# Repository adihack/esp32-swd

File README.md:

# esp-swd

**esp-swd** is an ESP32-S3 based dual-target SWD flasher and UART bridge with DUT isolation: open hardware, firmware,
a portable C library and a Python host library. It is built for CI and production benches, where a probe stays
plugged in for weeks and flashes the same known 3.3 V targets over and over.

The r5 board sits between a host PC (USB-C) and a device under test (DUT) that carries two MCUs, one per channel.
It does three things:
- programs each MCU over its own SWD port;
- bridges each DUT UART to the host;
- on command, opens analog switches on every DUT line, so the DUT's sleep current can be measured without leakage
  through the tool.

## Status (2026-11-11): MVP
Firmware 0.5.0 (protocol 5) with the `esw` host tools covers the first usable scope:
- **Two SWD channels**, two DUTs flashed at once: `esw flash A=app.hex B=fw.hex`.
- **Two DUT UARTs as terminal devices**, up to 1 Mbaud each, full duplex: the daemon `esw serve` serves them as
  `ttyA`/`ttyB` for picocom, minicom, screen, pyserial and the like.
- **Isolation control:**
  - semi-automatic: the switches close only while used and only with the DUT powered;
  - direct: switch modes `auto`/`on`/`off` per group, from the CLI or Python.
- **Firmware update over USB:** `esw update`, esptool through the chip's USB-Serial-JTAG. No buttons, and it
  recovers even a hung firmware.

Usage: **`host/python/README.md`**. State, open items and next steps: **`docs/status.md`**. Hardware tests:
**`docs/testing.md`**. Everything below is tested on hardware.

Earlier results (board r5, channel A, nRF52840 DK):
- **Isolation interlock:** VTref is checked before any signal switch closes. The switches reopen on VTref loss, host
  loss, reboot and firmware panic.
- **SWD engines:** an ESP32-S3 dedicated-GPIO engine up to 8 MHz (10 MHz cap), and a portable bit-bang fallback.
  Soak: about 3 M packets each at 8 MHz and 10 MHz, 0 errors.
- **Flashing:** 1 MB of random data on an nRF52840 takes **3.42 s** in total: mass erase 0.17 s, program 3.08 s,
  on-target CRC-32 verify 0.17 s. The data path is PC → USB → ESP32-S3 → SWD → NVMC.
- **UART bridge (channel A):** byte-exact at 115200, 460800 and 1 Mbaud, full duplex.
  - A 1 MB stream arrived intact while SWD reads ran in parallel and the host stopped reading for 250 ms.
  - With the switches open nothing gets through, and writes are refused.
- **Firmware update:** `idf.py flash` over USB while the firmware runs; two OTA slots with rollback.
- **Target modules (2026-11-10):** nRF52, **nRF5340** (application and network core) and **STM32U575/585**, plus a
  generic Cortex-M fallback. Measured, erase + program + on-target CRC verify: nRF5340 1 MB app image 3.2 s, network
  core 256 KB 0.71 s; STM32U585 2 MB 7.0 s through a streaming RAM loader (322 KB/s), a real 1.2 MB image 4.2 s;
  RDP level 1 → 0 unlock tested.
- **Parallel channels:** one SWD worker per channel on its own CPU core. nRF5340 + STM32U585 flashed at once:
  5.5 s against 7.5 s one after the other (now limited by the USB-Serial-JTAG link, about 485 KB/s).

- **Host daemon and TTYs (2026-11-11):** ttyA ↔ ttyB cabled across the two UART headers, both directions at once,
  byte-exact at up to 2 Mbaud; at 1 Mbaud (97 KB/s each way) also while both DUTs flash. Both DUTs at once with
  `esw flash`: 5.6 s against 8.6 s one after the other.
  Programs share the board through the daemon (per-channel ownership, cleanup after a crash), and it survives board
  reboots and firmware updates.

| Not done yet |
|---|
| SWO |
| USB-OTG (TinyUSB): native CDC TTYs, vendor bulk interface, optional CMSIS-DAP v2; OTA over the protocol |
| STM32U5 with TrustZone on, external-flash loaders on the streaming ABI, nRF5340 network-core fast path test |
| multi-day soak |

Hardware is frozen at r5 (design revision d, JLCPCB, 2026-10-23). The two assembled boards carry
ESP32-S3-WROOM-1-**N4** modules (4 MB flash, no PSRAM), not the N16 in the BOM.

## Repository layout
| Path | Content |
|---|---|
| `lib/` | **Portable C11 library**: SWD/ADIv5, Cortex-M control, generic RAM-loader runtime (call and streaming ABIs), on-target CRC verify, target-module interface and the nRF52 module, isolation interlock, framed host protocol. No RTOS, no malloc. See `lib/README.md` |
| `ports/esp32s3/` | ESP32-S3 port: dedicated-GPIO SWD engine, pins, ADC, clock |
| `boards/r5/` | r5 board layer: pin map, switch groups, VTref divider, safe defaults |
| `app/` | ESP-IDF v6 firmware for r5 (USB-Serial-JTAG transport). See `app/README.md` |
| `host/python/` | Python host library and CLI (`esw`), daemon with the TTY bridge (`esw serve`), examples: flashing, speed test, PHY benchmark, UART and TTY self-tests, robustness checks. See `host/python/README.md` |
| `host/udev/`, `host/systemd/` | udev rule for the board; systemd user unit for the daemon |
| `loaders/` | Target-side loader sources; `crc32/build.py` (built-in CRC loader) and `stm32u5/build.py` (STM32U5 streaming flash loader) rebuild and verify them in an emulator |
| `testfw/` | Bare-metal test firmware for DUTs, e.g. `nrf52840_uart/` for the UART hardware test |
| `tests/` | Host unit tests against a bit-level SWD target simulator (`tests/sim/`); CI in `.github/workflows/ci.yml` |
| `docs/status.md`, `docs/testing.md` | **Start here for a new session:** status, decisions, next steps; every test with wiring and last results |
| `docs/hardware-reference.md` | **Start here for hardware.** Pin map, signal chains, polarities, connectors, test pads, interlock rules, boot notes, bring-up results |
| `docs/firmware-architecture.md` | Firmware architecture, reliability plan, milestones, decisions |
| `docs/hardware/` | Design brief, hardware architecture history, PCB layout notes |
| `docs/datasheets/` | Links to the vendor datasheets (not redistributed) |
| `hardware/rev5/` | r5 schematic PDF, KiCad 10 project as built, the exact JLCPCB production package |
| `firmware/bringup/`, `firmware/poc_swd/` | MicroPython bring-up blink and the first SWD board test (kept for reference) |

## New machine
Linux (Ubuntu or similar), Python ≥ 3.9. From a fresh clone:
```
git clone https://github.com/adihack/esp32-swd.git && cd esp32-swd

# 1. Python venv: build tools, host tools (`esw`), esptool; unicorn/capstone only for rebuilding loaders
python3 -m venv .venv
.venv/bin/pip install cmake ninja pyserial esptool unicorn capstone
.venv/bin/pip install -e host/python

# 2. USB access without sudo, no ModemManager probing (then re-plug the board)
sudo cp host/udev/60-esp-swd.rules /etc/udev/rules.d/ && sudo udevadm control --reload && sudo udevadm trigger

# 3. Library tests (no hardware)
PATH=$PWD/.venv/bin:$PATH cmake -S . -B build -G Ninja && cmake --build build && ctest --test-dir build
.venv/bin/python -m unittest discover -s host/python/tests

# 4. Firmware: ESP-IDF v6.0.3 (about 5 GB with tools)
git clone -b v6.0.3 --recursive https://github.com/espressif/esp-idf.git ~/esp/esp-idf-v6.0.3
~/esp/esp-idf-v6.0.3/install.sh esp32s3
. ~/esp/esp-idf-v6.0.3/export.sh && export PATH="$PATH:$PWD/.venv/bin"   # append the venv, never prepend
(cd app && idf.py build)
.venv/bin/esw update app/build          # or: cd app && idf.py -p /dev/ttyACM0 flash
.venv/bin/esw info
```
- No buttons are needed: USB-Serial-JTAG resets the chip into the ROM downloader in hardware. The board
  enumerates as `303a:1001`.
- Optional: the Arm GNU toolchain (15.3.rel2, from developer.arm.com, unpacked to
  `~/arm/arm-gnu-toolchain-15.3.rel2-x86_64-arm-none-eabi`, or set `ARM_GCC_BIN`). Needed only to rebuild the
  target-side loaders (`loaders/*/build.py`) and the DUT test firmware (`testfw/`, used by `uart_test.py`).

**Where to go next:** `docs/status.md` (where the project stands, what is next), `docs/testing.md` (every hardware
test with wiring and expected results), `host/python/README.md` (using `esw`).

## Quick start
```
esw serve &                                         # TTYs: $XDG_RUNTIME_DIR/esp-swd/<board>/ttyA, ttyB
esw info                                            # channels, switches, modes, TTYs
esw flash A=app.hex B=stm32.hex                     # both channels at once, CRC-verified
esw flash A1=net.hex                                # nRF5340 network core
esw mode B uart off                                 # isolation switch modes: auto | on | off
esw update app/build                                # board firmware over USB
esw stop                                            # stop the daemon
```
Examples (they also run through the daemon; wiring and expected results in `docs/testing.md`):
```
.venv/bin/python host/python/examples/flash_image.py --info --channel B      # identify a target, print its memory map
.venv/bin/python host/python/examples/parallel_flash.py --a app_a.hex --b app_b.hex   # benchmark, both channels
.venv/bin/python host/python/examples/tty_loopback.py --cross               # UART A <-> B through the TTYs
.venv/bin/python host/python/examples/nrf52_blinky.py --channel A          # nRF52840 DK: flash and watch it run
```
nRF5340: flash only images with Nordic's startup code (see `app/README.md`, "nRF5340 APPROTECT trap").
`--allow-erase` mass-erases a locked chip; without it, a locked chip is left alone.

## Hardware in one screen
| Function | Channel A | Channel B |
|---|---|---|
| SWDIO / SWCLK | GPIO4 / GPIO5 | GPIO11 / GPIO12 |
| SWO (in) | GPIO6 | GPIO14 |
| nRESET drive (high = assert) / sense | GPIO7 / GPIO15 | GPIO21 / GPIO47 |
| UART TX / RX | GPIO16 / GPIO17 | GPIO48 / GPIO35 |
| VTref ADC (reads VTref/2) | GPIO8 (ADC1_CH7) | GPIO1 (ADC1_CH0) |
| EN_SWD / EN_UART / EN_VTREF (active high) | GPIO9 / GPIO46 / GPIO10 | GPIO40 / GPIO41 / GPIO42 |

- Status LED: GPIO2, active high.
- USB: native, on GPIO19/20.
- No buttons.
- DUT I/O is 3.3 V only; there are no level translators.
- Every switch is **open by default** (100 kΩ pull-downs on the enables).
- Firmware must close EN_VTREF and see the DUT powered **before** closing the SWD or UART groups. Otherwise the tool
  back-powers an unpowered DUT.

All details, with the reasons, are in `docs/hardware-reference.md`.

## License
MIT, see `LICENSE`. This covers the firmware, library, host tools, documentation and the r5 hardware design files.
Vendor datasheets and the USB-C connector's 3D model are not part of the repository; see `docs/datasheets/README.md`.

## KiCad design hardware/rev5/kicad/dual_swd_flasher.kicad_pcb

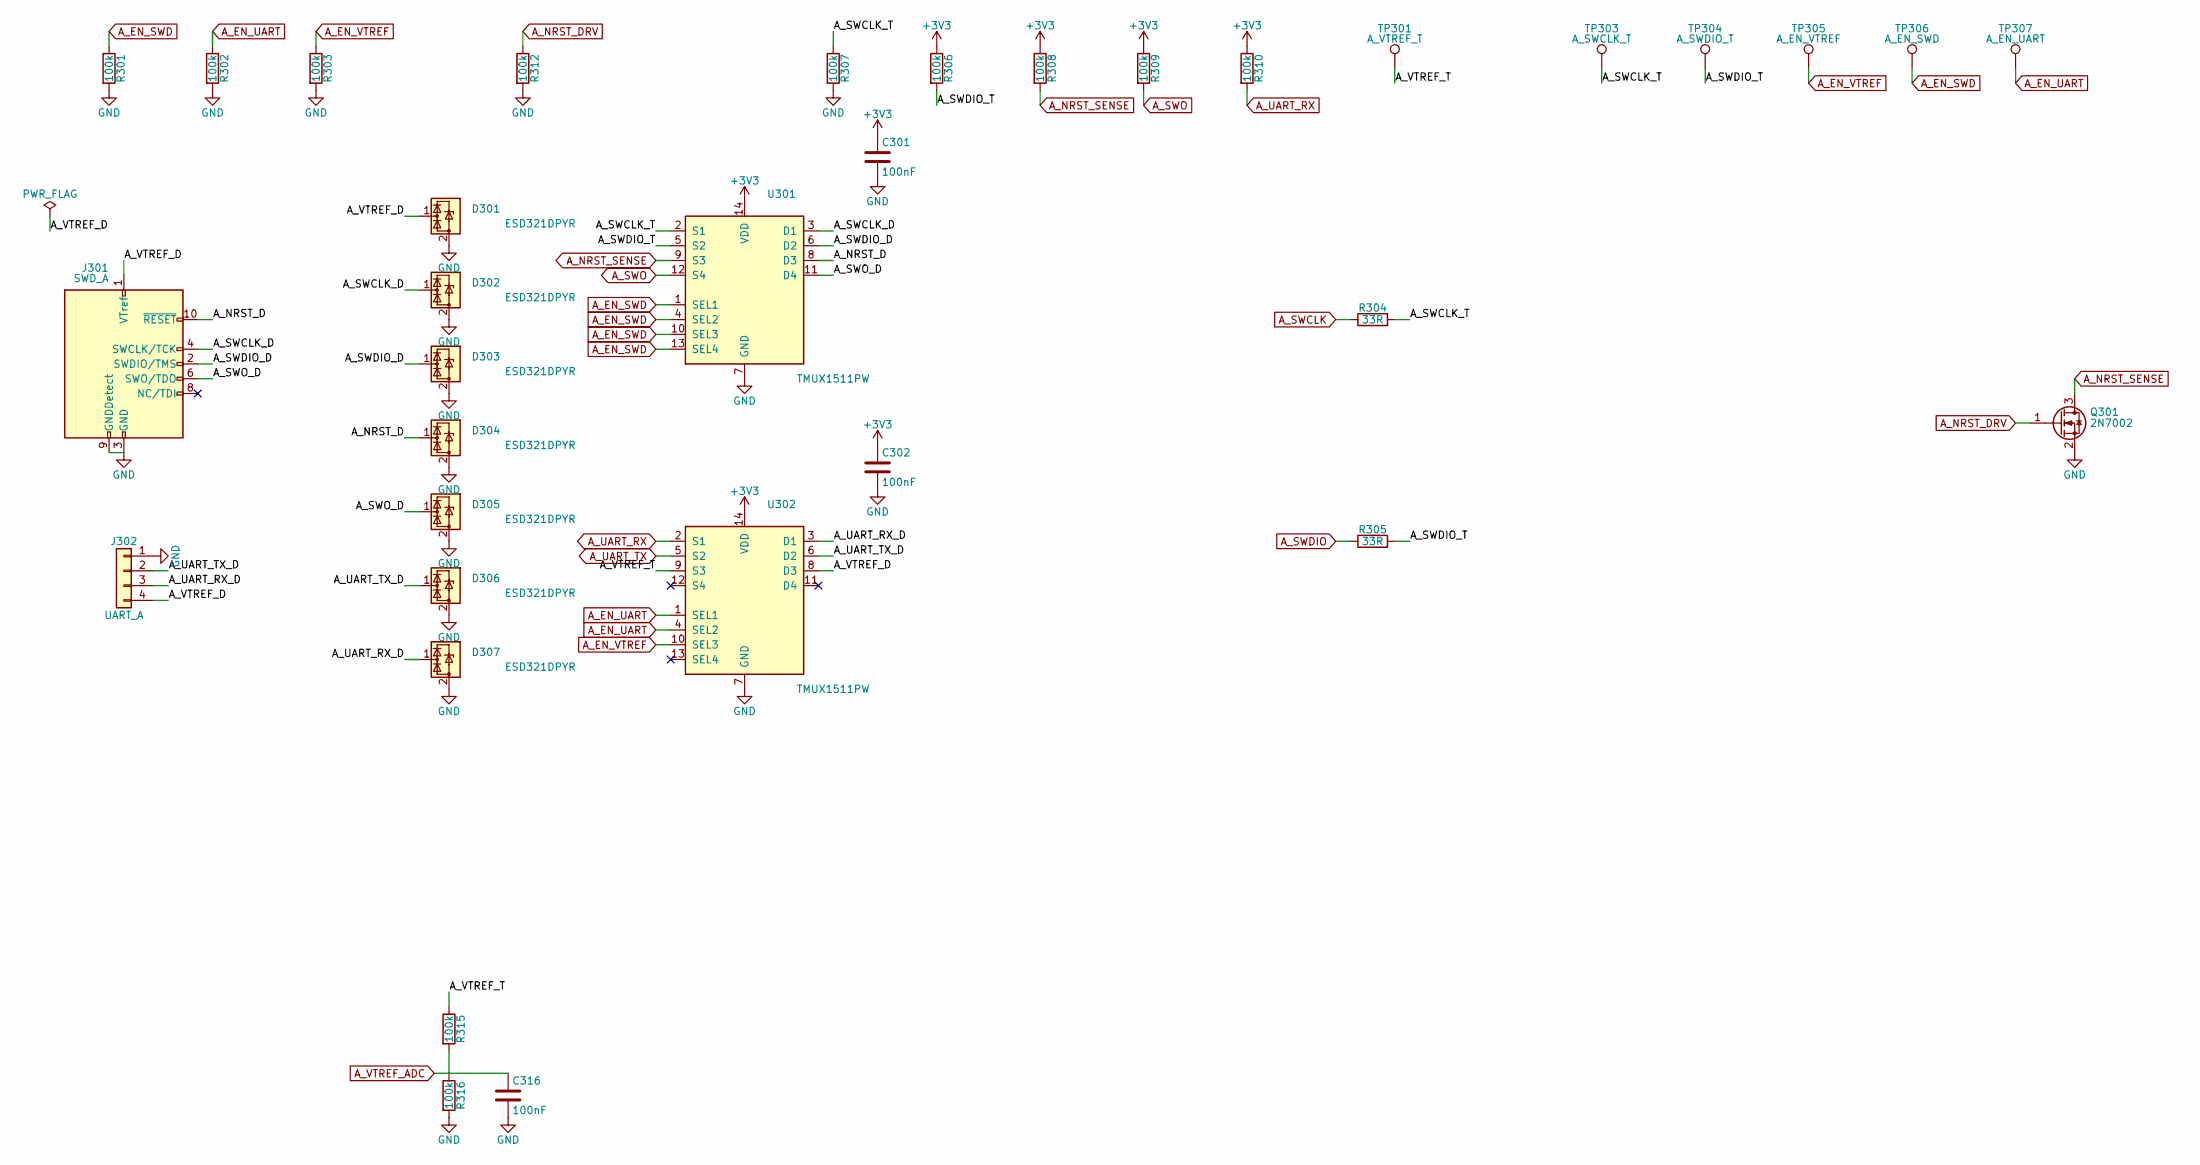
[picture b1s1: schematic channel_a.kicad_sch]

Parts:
C301, C302, C316: 100nF; C_0402_1005Metric; LCSC C1525
D301, D302, D303, D304, D305, D306, D307: ESD321DPYR; Texas_DPY0002A_0.6x1mm_P0.65mm; LCSC C2868952
J301: SWD_A; PinHeader_2x05_P1.27mm_Vertical_SMD; LCSC C3975188
J302: UART_A; PinHeader_1x04_P2.54mm_Vertical; LCSC C2691448
Q301: 2N7002; SOT-23; LCSC C8545
R301, R302, R303, R306, R307, R308, R309, R310, R312, R315, R316: 100k; R_0402_1005Metric; LCSC C25741
R304, R305: 33R; R_0402_1005Metric; LCSC C25105
TP301: A_VTREF_T; TestPoint_Pad_D1.0mm
TP303: A_SWCLK_T; TestPoint_Pad_D1.0mm
TP304: A_SWDIO_T; TestPoint_Pad_D1.0mm
TP305: A_EN_VTREF; TestPoint_Pad_D1.0mm
TP306: A_EN_SWD; TestPoint_Pad_D1.0mm
TP307: A_EN_UART; TestPoint_Pad_D1.0mm
U301, U302: TMUX1511PW; TSSOP-14_4.4x5mm_P0.65mm; LCSC C2866750

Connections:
+3V3: C301.1, C302.1, R306.1, R308.1, R309.1, R310.1, U301.14 (VDD), U302.14 (VDD); also elsewhere on the board
/Channel A/A_NRST_D: D304.1 (I/O), J301.10 (~RESET), U301.8 (D3)
/Channel A/A_SWCLK_D: D302.1 (I/O), J301.4 (SWCLK/TCK), U301.3 (D1)
/Channel A/A_SWCLK_T: R304.2, R307.1, TP303.1 (1_1), U301.2 (S1)
/Channel A/A_SWDIO_D: D303.1 (I/O), J301.2 (SWDIO/TMS), U301.6 (D2)
/Channel A/A_SWDIO_T: R305.2, R306.2, TP304.1 (1_1), U301.5 (S2)
/Channel A/A_SWO_D: D305.1 (I/O), J301.6 (SWO/TDO), U301.11 (D4)
/Channel A/A_UART_RX_D: D307.1 (I/O), J302.3, U302.3 (D1)
/Channel A/A_UART_TX_D: D306.1 (I/O), J302.2, U302.6 (D2)
/Channel A/A_VTREF_D: D301.1 (I/O), J301.1 (VTref), J302.4, U302.8 (D3)
/Channel A/A_VTREF_T: R315.1, TP301.1 (1_1), U302.9 (S3)
A_EN_SWD: R301.1, TP306.1 (1_1), U301.1 (SEL1), U301.4 (SEL2), U301.10 (SEL3), U301.13 (SEL4); also elsewhere on the board
A_EN_UART: R302.1, TP307.1 (1_1), U302.1 (SEL1), U302.4 (SEL2); also elsewhere on the board
A_EN_VTREF: R303.1, TP305.1 (1_1), U302.10 (SEL3); also elsewhere on the board
A_NRST_DRV: Q301.1 (G), R312.1; also elsewhere on the board
A_NRST_SENSE: Q301.3 (D), R308.2, U301.9 (S3); also elsewhere on the board
A_SWCLK: R304.1; also elsewhere on the board
A_SWDIO: R305.1; also elsewhere on the board
A_SWO: R309.2, U301.12 (S4); also elsewhere on the board
A_UART_RX: R310.2, U302.2 (S1); also elsewhere on the board
A_UART_TX: U302.5 (S2); also elsewhere on the board
A_VTREF_ADC: C316.1, R315.2, R316.1; also elsewhere on the board
GND: C301.2, C302.2, C316.2, D301.2 (GND), D302.2 (GND), D303.2 (GND), D304.2 (GND), D305.2 (GND), D306.2 (GND), D307.2 (GND), J301.3 (GND), J301.5 (GND), J301.9 (GNDDetect), J302.1, Q301.2 (S), R301.2, R302.2, R303.2, R307.2, R312.2, R316.2, U301.7 (GND), U302.7 (GND); also elsewhere on the board

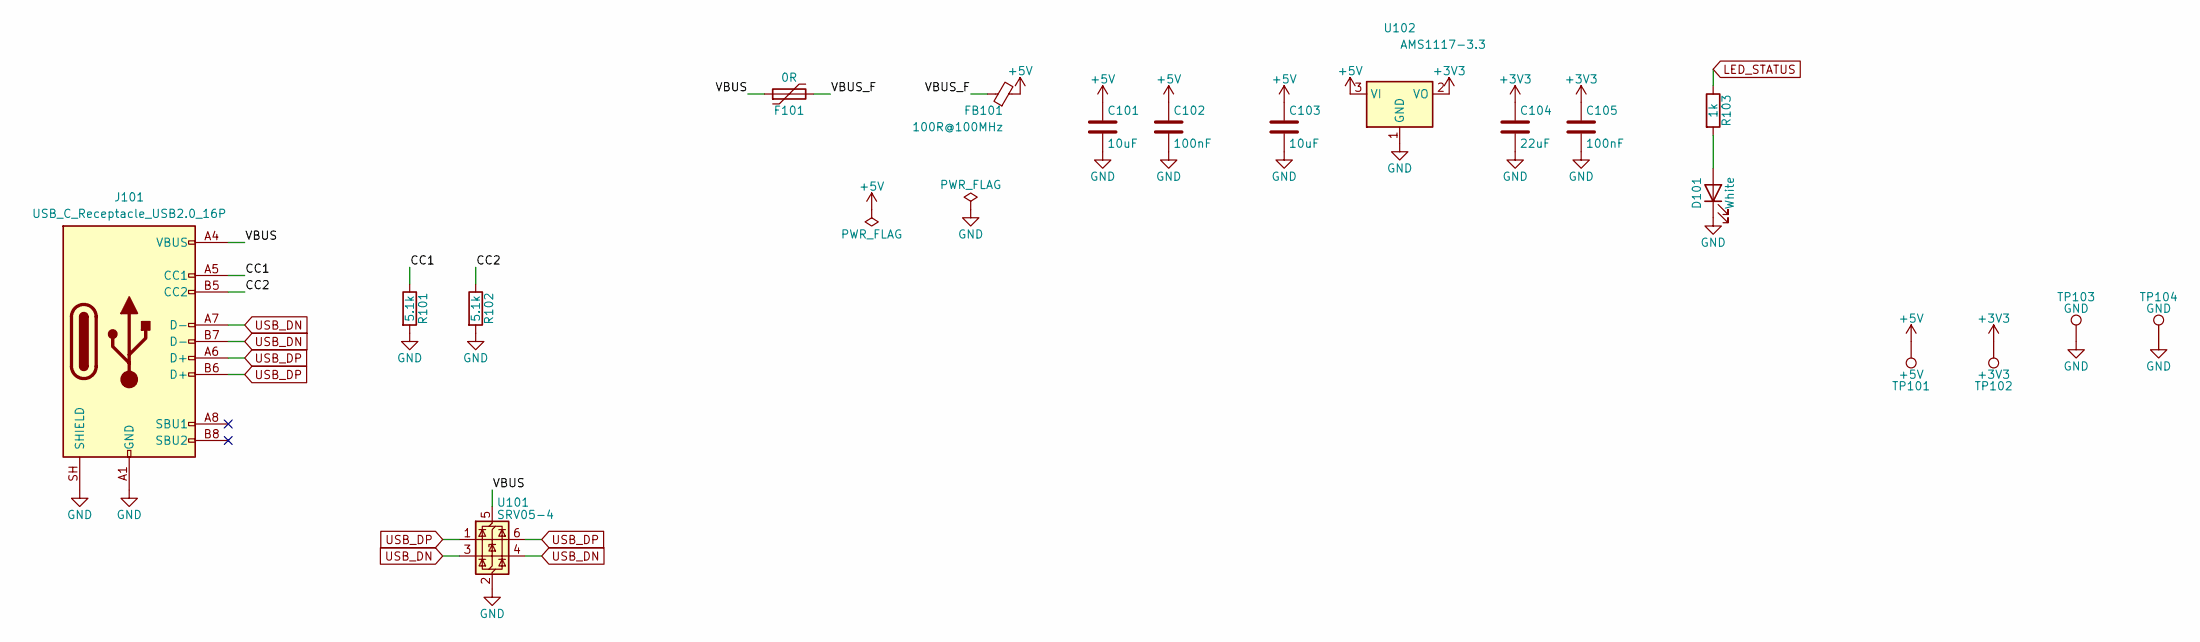
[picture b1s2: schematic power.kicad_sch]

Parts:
C101, C103: 10uF; C_0805_2012Metric; LCSC C15850
C102, C105: 100nF; C_0402_1005Metric; LCSC C1525
C104: 22uF; C_0805_2012Metric; LCSC C45783
D101: White; LED_0603_1608Metric; LCSC C2290
F101: 0R; Fuse_1206_3216Metric; LCSC C17888
FB101: 100R@100MHz; L_0805_2012Metric; LCSC C1015
J101: USB_C_Receptacle_USB2.0_16P; USB_C_Receptacle_HRO_TYPE-C-31-M-12; LCSC C165948
R101, R102: 5.1k; R_0402_1005Metric; LCSC C25905
R103: 1k; R_0402_1005Metric; LCSC C11702
TP101: +5V; TestPoint_Pad_D1.0mm
TP102: +3V3; TestPoint_Pad_D1.0mm
TP103, TP104: GND; TestPoint_Pad_D1.0mm
U101: SRV05-4; SOT-23-6; LCSC C7420376
U102: AMS1117-3.3; SOT-223-3_TabPin2; LCSC C6186

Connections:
+3V3: C104.1, C105.1, TP102.1 (1_1), U102.2 (VO); also elsewhere on the board
+5V: C101.1, C102.1, C103.1, FB101.2, TP101.1 (1_1), U102.3 (VI); also elsewhere on the board
/Power/CC1: J101.A5 (CC1), R101.1
/Power/CC2: J101.B5 (CC2), R102.1
/Power/VBUS: F101.1, J101.A4 (VBUS), J101.A9 (VBUS), J101.B4 (VBUS), J101.B9 (VBUS), U101.5 (VBUS)
/Power/VBUS_F: F101.2, FB101.1
GND: C101.2, C102.2, C103.2, C104.2, C105.2, D101.1 (K), J101.A1 (GND), J101.A12 (GND), J101.B1 (GND), J101.B12 (GND), J101.SH (SHIELD), R101.2, R102.2, TP103.1 (1_1), TP104.1 (1_1), U101.2 (GND), U102.1 (GND); also elsewhere on the board
LED_STATUS: R103.1; also elsewhere on the board
unnamed: D101.2 (A), R103.2
USB_DN: J101.A7 (D-), J101.B7 (D-), U101.3 (I/O2), U101.4 (I/O2); also elsewhere on the board
USB_DP: J101.A6 (D+), J101.B6 (D+), U101.1 (I/O1), U101.6 (I/O1); also elsewhere on the board

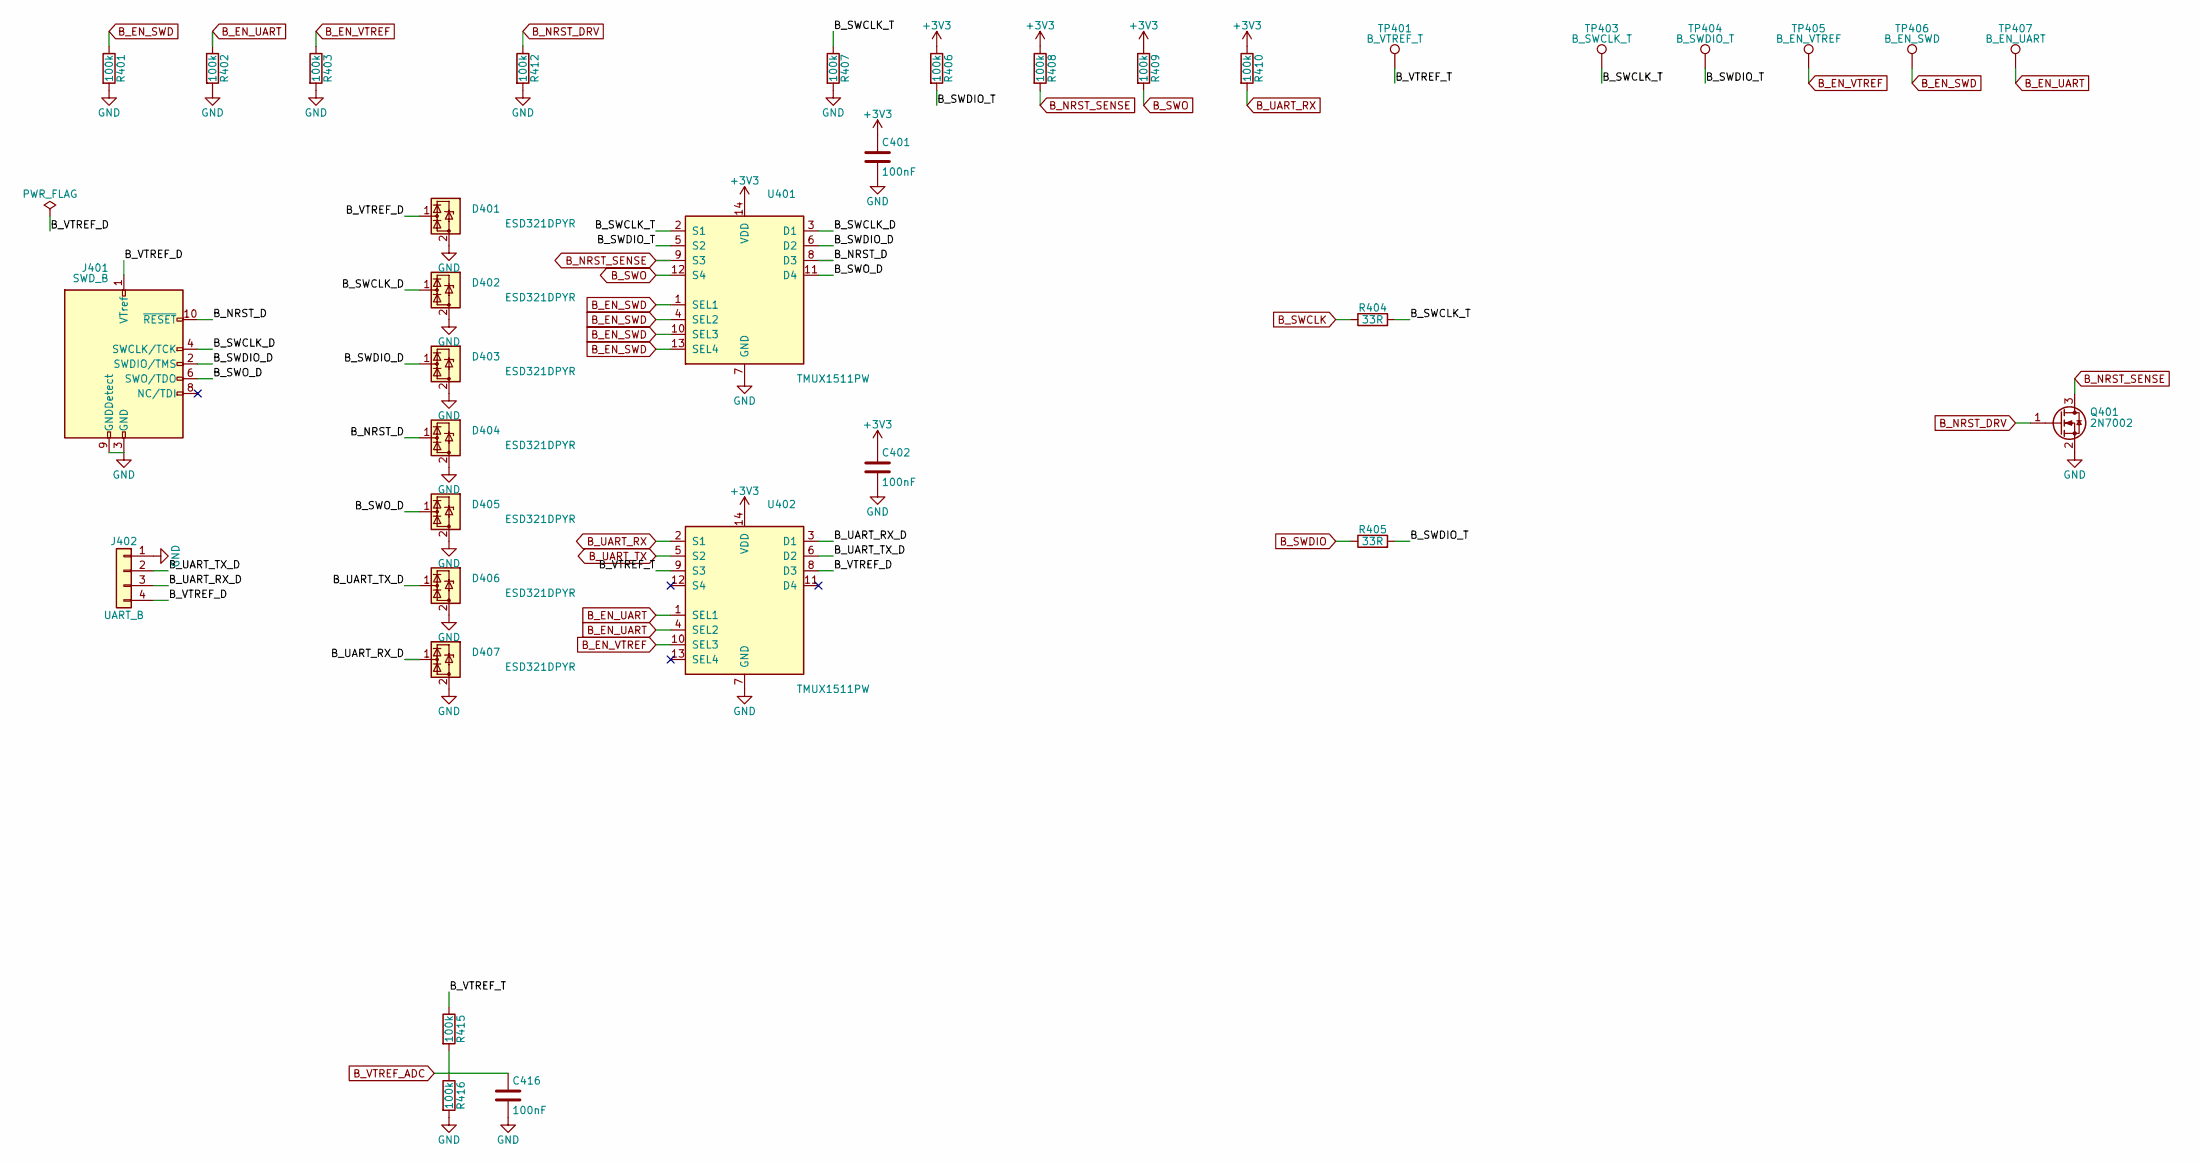
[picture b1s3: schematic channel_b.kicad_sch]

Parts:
C401, C402, C416: 100nF; C_0402_1005Metric; LCSC C1525
D401, D402, D403, D404, D405, D406, D407: ESD321DPYR; Texas_DPY0002A_0.6x1mm_P0.65mm; LCSC C2868952
J401: SWD_B; PinHeader_2x05_P1.27mm_Vertical_SMD; LCSC C3975188
J402: UART_B; PinHeader_1x04_P2.54mm_Vertical; LCSC C2691448
Q401: 2N7002; SOT-23; LCSC C8545
R401, R402, R403, R406, R407, R408, R409, R410, R412, R415, R416: 100k; R_0402_1005Metric; LCSC C25741
R404, R405: 33R; R_0402_1005Metric; LCSC C25105
TP401: B_VTREF_T; TestPoint_Pad_D1.0mm
TP403: B_SWCLK_T; TestPoint_Pad_D1.0mm
TP404: B_SWDIO_T; TestPoint_Pad_D1.0mm
TP405: B_EN_VTREF; TestPoint_Pad_D1.0mm
TP406: B_EN_SWD; TestPoint_Pad_D1.0mm
TP407: B_EN_UART; TestPoint_Pad_D1.0mm
U401, U402: TMUX1511PW; TSSOP-14_4.4x5mm_P0.65mm; LCSC C2866750

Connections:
+3V3: C401.1, C402.1, R406.1, R408.1, R409.1, R410.1, U401.14 (VDD), U402.14 (VDD); also elsewhere on the board
/Channel B/B_NRST_D: D404.1 (I/O), J401.10 (~RESET), U401.8 (D3)
/Channel B/B_SWCLK_D: D402.1 (I/O), J401.4 (SWCLK/TCK), U401.3 (D1)
/Channel B/B_SWCLK_T: R404.2, R407.1, TP403.1 (1_1), U401.2 (S1)
/Channel B/B_SWDIO_D: D403.1 (I/O), J401.2 (SWDIO/TMS), U401.6 (D2)
/Channel B/B_SWDIO_T: R405.2, R406.2, TP404.1 (1_1), U401.5 (S2)
/Channel B/B_SWO_D: D405.1 (I/O), J401.6 (SWO/TDO), U401.11 (D4)
/Channel B/B_UART_RX_D: D407.1 (I/O), J402.3, U402.3 (D1)
/Channel B/B_UART_TX_D: D406.1 (I/O), J402.2, U402.6 (D2)
/Channel B/B_VTREF_D: D401.1 (I/O), J401.1 (VTref), J402.4, U402.8 (D3)
/Channel B/B_VTREF_T: R415.1, TP401.1 (1_1), U402.9 (S3)
B_EN_SWD: R401.1, TP406.1 (1_1), U401.1 (SEL1), U401.4 (SEL2), U401.10 (SEL3), U401.13 (SEL4); also elsewhere on the board
B_EN_UART: R402.1, TP407.1 (1_1), U402.1 (SEL1), U402.4 (SEL2); also elsewhere on the board
B_EN_VTREF: R403.1, TP405.1 (1_1), U402.10 (SEL3); also elsewhere on the board
B_NRST_DRV: Q401.1 (G), R412.1; also elsewhere on the board
B_NRST_SENSE: Q401.3 (D), R408.2, U401.9 (S3); also elsewhere on the board
B_SWCLK: R404.1; also elsewhere on the board
B_SWDIO: R405.1; also elsewhere on the board
B_SWO: R409.2, U401.12 (S4); also elsewhere on the board
B_UART_RX: R410.2, U402.2 (S1); also elsewhere on the board
B_UART_TX: U402.5 (S2); also elsewhere on the board
B_VTREF_ADC: C416.1, R415.2, R416.1; also elsewhere on the board
GND: C401.2, C402.2, C416.2, D401.2 (GND), D402.2 (GND), D403.2 (GND), D404.2 (GND), D405.2 (GND), D406.2 (GND), D407.2 (GND), J401.3 (GND), J401.5 (GND), J401.9 (GNDDetect), J402.1, Q401.2 (S), R401.2, R402.2, R403.2, R407.2, R412.2, R416.2, U401.7 (GND), U402.7 (GND); also elsewhere on the board

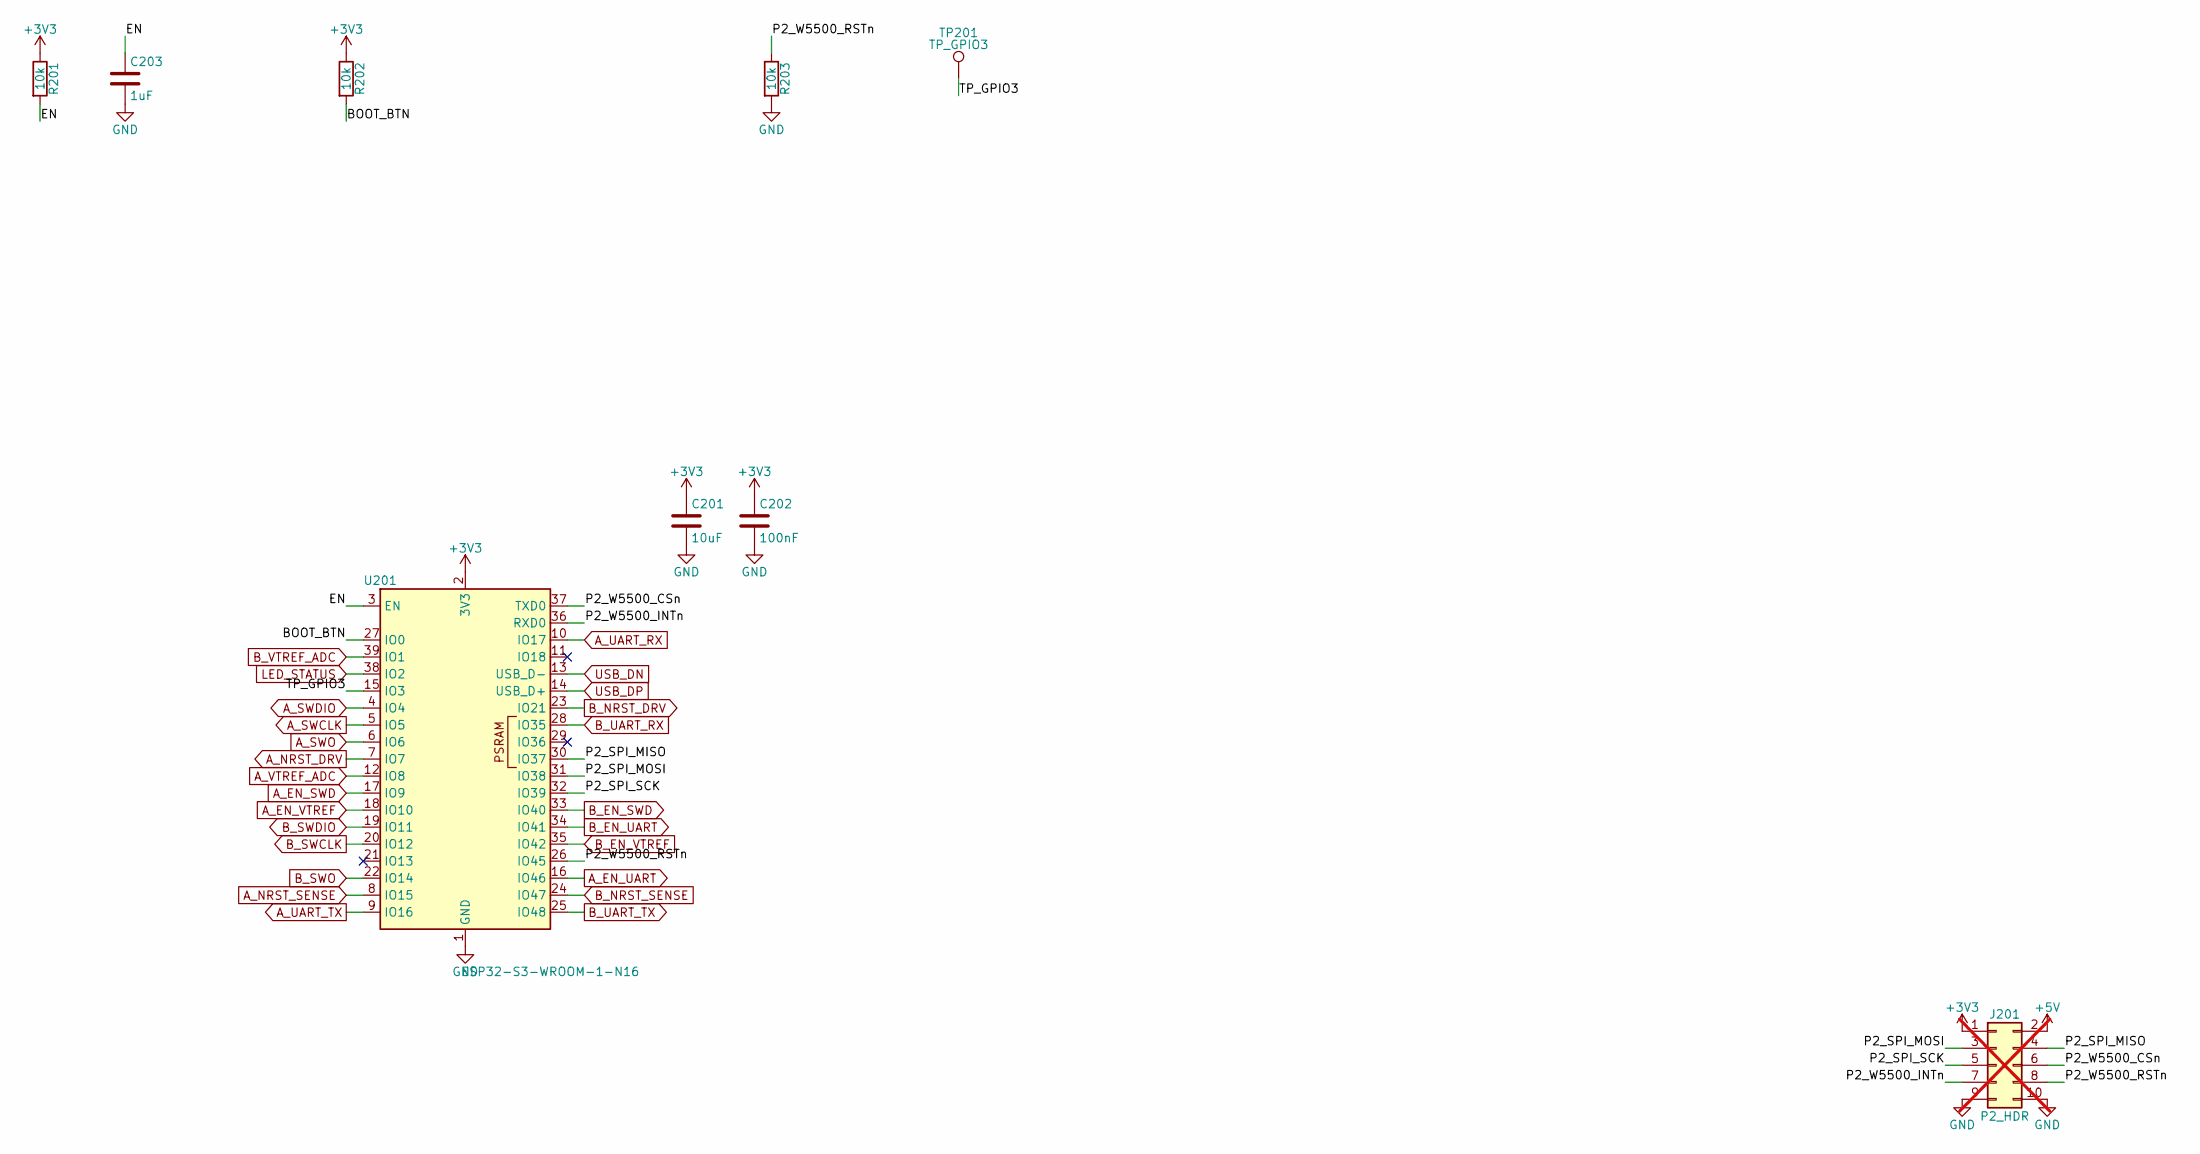
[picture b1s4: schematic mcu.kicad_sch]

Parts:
C201: 10uF; C_0805_2012Metric; LCSC C15850
C202: 100nF; C_0402_1005Metric; LCSC C1525
C203: 1uF; C_0402_1005Metric; LCSC C52923
J201: P2_HDR; PinHeader_2x05_P2.54mm_Vertical; not fitted
R201, R202, R203: 10k; R_0402_1005Metric; LCSC C25744
TP201: TP_GPIO3; TestPoint_Pad_D1.0mm
U201: ESP32-S3-WROOM-1-N16; ESP32-S3-WROOM-1; LCSC C2913199

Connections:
+3V3: C201.1, C202.1, J201.1, R201.1, R202.1, U201.2 (3V3); also elsewhere on the board
+5V: J201.2; also elsewhere on the board
/MCU/BOOT_BTN: R202.2, U201.27 (IO0)
/MCU/EN: C203.1, R201.2, U201.3 (EN)
/MCU/P2_SPI_MISO: J201.4, U201.30 (IO37)
/MCU/P2_SPI_MOSI: J201.3, U201.31 (IO38)
/MCU/P2_SPI_SCK: J201.5, U201.32 (IO39)
/MCU/P2_W5500_CSn: J201.6, U201.37 (TXD0)
/MCU/P2_W5500_INTn: J201.7, U201.36 (RXD0)
/MCU/P2_W5500_RSTn: J201.8, R203.1, U201.26 (IO45)
/MCU/TP_GPIO3: TP201.1 (1_1), U201.15 (IO3)
A_EN_SWD: U201.17 (IO9); also elsewhere on the board
A_EN_UART: U201.16 (IO46); also elsewhere on the board
A_EN_VTREF: U201.18 (IO10); also elsewhere on the board
A_NRST_DRV: U201.7 (IO7); also elsewhere on the board
A_NRST_SENSE: U201.8 (IO15); also elsewhere on the board
A_SWCLK: U201.5 (IO5); also elsewhere on the board
A_SWDIO: U201.4 (IO4); also elsewhere on the board
A_SWO: U201.6 (IO6); also elsewhere on the board
A_UART_RX: U201.10 (IO17); also elsewhere on the board
A_UART_TX: U201.9 (IO16); also elsewhere on the board
A_VTREF_ADC: U201.12 (IO8); also elsewhere on the board
B_EN_SWD: U201.33 (IO40); also elsewhere on the board
B_EN_UART: U201.34 (IO41); also elsewhere on the board
B_EN_VTREF: U201.35 (IO42); also elsewhere on the board
B_NRST_DRV: U201.23 (IO21); also elsewhere on the board
B_NRST_SENSE: U201.24 (IO47); also elsewhere on the board
B_SWCLK: U201.20 (IO12); also elsewhere on the board
B_SWDIO: U201.19 (IO11); also elsewhere on the board
B_SWO: U201.22 (IO14); also elsewhere on the board
B_UART_RX: U201.28 (IO35); also elsewhere on the board
B_UART_TX: U201.25 (IO48); also elsewhere on the board
B_VTREF_ADC: U201.39 (IO1); also elsewhere on the board
GND: C201.2, C202.2, C203.2, J201.9, J201.10, R203.2, U201.1 (GND), U201.40 (GND), U201.41 (GND); also elsewhere on the board
LED_STATUS: U201.38 (IO2); also elsewhere on the board
USB_DN: U201.13 (USB_D-); also elsewhere on the board
USB_DP: U201.14 (USB_D+); also elsewhere on the board

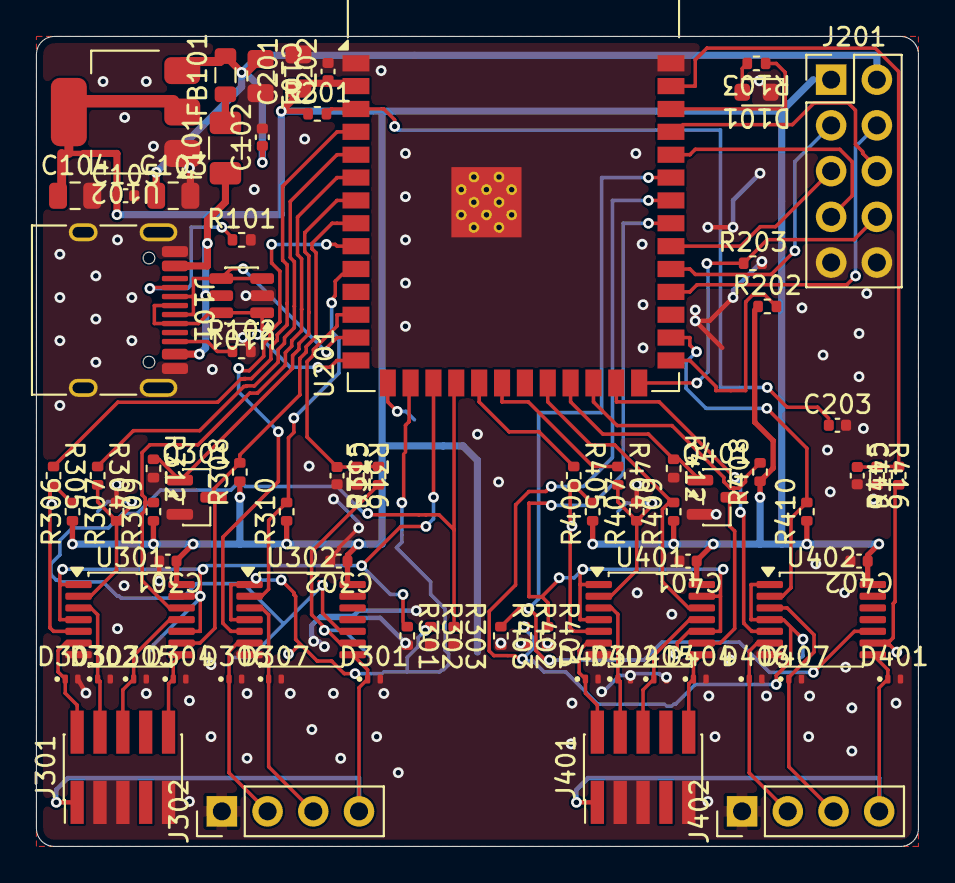
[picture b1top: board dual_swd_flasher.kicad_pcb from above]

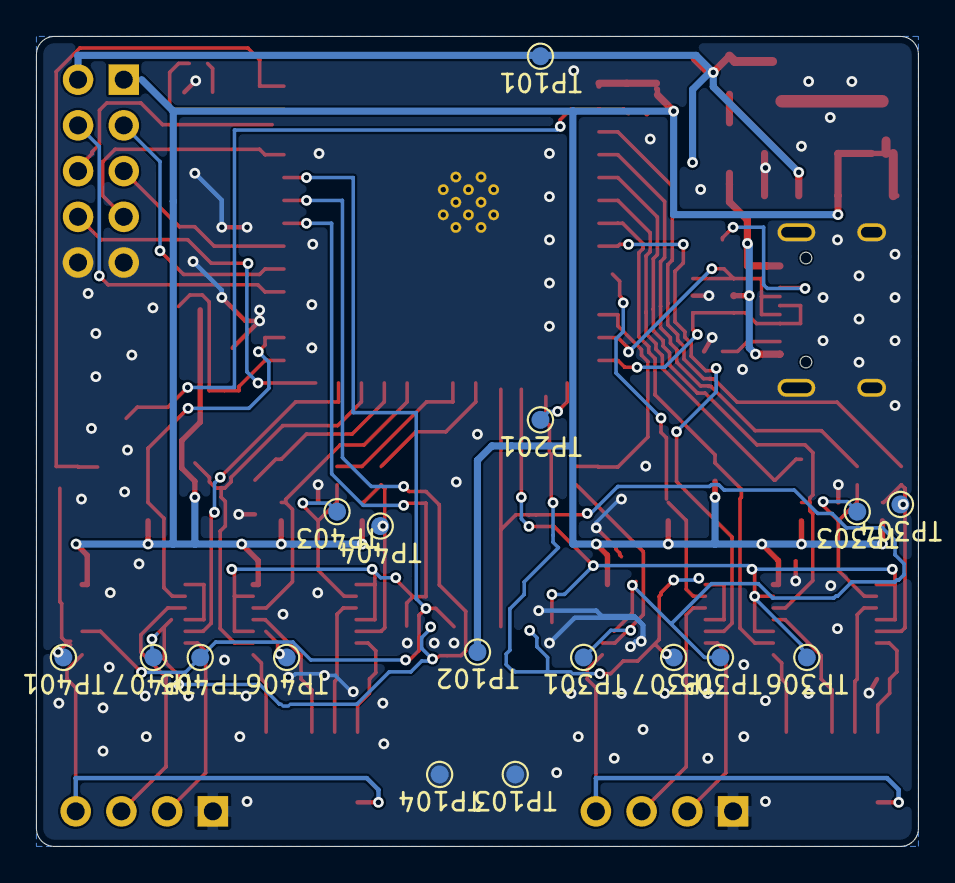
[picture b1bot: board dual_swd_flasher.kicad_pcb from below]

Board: 2 copper layers, 49.0 x 45.0 mm, 95 parts (17 on the bottom side), 62 nets.

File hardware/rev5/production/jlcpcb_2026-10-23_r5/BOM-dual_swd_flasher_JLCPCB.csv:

"Comment","Designator","Footprint","LCSC Part #"
"10uF","C101,C103,C201","Capacitor_SMD:C_0805_2012Metric","C15850"
"100nF","C102,C105,C202,C301,C302,C316,C401,C402,C416","Capacitor_SMD:C_0402_1005Metric","C1525"
"22uF","C104","Capacitor_SMD:C_0805_2012Metric","C45783"
"1uF","C203","Capacitor_SMD:C_0402_1005Metric","C52923"
"White","D101","LED_SMD:LED_0603_1608Metric","C2290"
"ESD321DPYR","D301,D302,D303,D304,D305,D306,D307,D401,D402,D403,D404,D405,D406,D407","Package_SON:Texas_DPY0002A_0.6x1mm_P0.65mm","C2868952"
"0R","F101","Fuse:Fuse_1206_3216Metric","C17888"
"100R@100MHz","FB101","Inductor_SMD:L_0805_2012Metric","C1015"
"USB_C_Receptacle_USB2.0_16P","J101","Connector_USB:USB_C_Receptacle_HRO_TYPE-C-31-M-12","C165948"
"SWD_A/SWD_B","J301,J401","Connector_PinHeader_1.27mm:PinHeader_2x05_P1.27mm_Vertical_SMD","C3975188"
"2N7002","Q301,Q401","Package_TO_SOT_SMD:SOT-23","C8545"
"5.1k","R101,R102","Resistor_SMD:R_0402_1005Metric","C25905"
"1k","R103","Resistor_SMD:R_0402_1005Metric","C11702"
"10k","R201,R202,R203","Resistor_SMD:R_0402_1005Metric","C25744"
"100k","R301,R302,R303,R306,R307,R308,R309,R310,R312,R315,R316,R401,R402,R403,R406,R407,R408,R409,R410,R412,R415,R416","Resistor_SMD:R_0402_1005Metric","C25741"
"33R","R304,R305,R404,R405","Resistor_SMD:R_0402_1005Metric","C25105"
"SRV05-4","U101","Package_TO_SOT_SMD:SOT-23-6","C7420376"
"AMS1117-3.3","U102","Package_TO_SOT_SMD:SOT-223-3_TabPin2","C6186"
"TMUX1511PW","U301,U302,U401,U402","Package_SO:TSSOP-14_4.4x5mm_P0.65mm","C2866750"
